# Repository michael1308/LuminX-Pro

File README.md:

# LuminX-WLED
ESP32-based controller for individually addressable LED strips, compatible with WLED firmware.

# Features
-   ESP32-WROOM-32E
-   CH340E/G
-   USB C
-   Micro USB for power
-   2.1mm Barrel Jack w/ reversible polarity    
-   Screw Terminal power input
-   Current Measurement w/ INA219/INA180
-   5V Buck Converter
-   3.3V LDO
-   Microphone
-   IR Receiver
-   2x Digital out w/ Clock signal
-   Power Switching Relay
-   Temperature Sensor DS18B20
-   I2C Connector
-   ESP32 Debug Connector
-   Up to 10A

# Rev 1.0 (03.2023)
## Issues:
- Reverse Polarity Protection MOSFET reversed
- INA180 Resistor too large -> change to 10mOhm
- USBLC6 wrong footprint -> SOT-6

## Changes:
- Remove Micro USB
- Route Input Voltage directly to output
- Change reverse polarity protection to antiparallel diode (M7)
- Integrate PDM Microphone
- Better Integration for IR Sensor
- Better Integration for Temp Sensor
- 4 Output Channels
- Smaller Footprint
- Automotive or Glass fuse?
- Separate board for guitar -> LuminX ??

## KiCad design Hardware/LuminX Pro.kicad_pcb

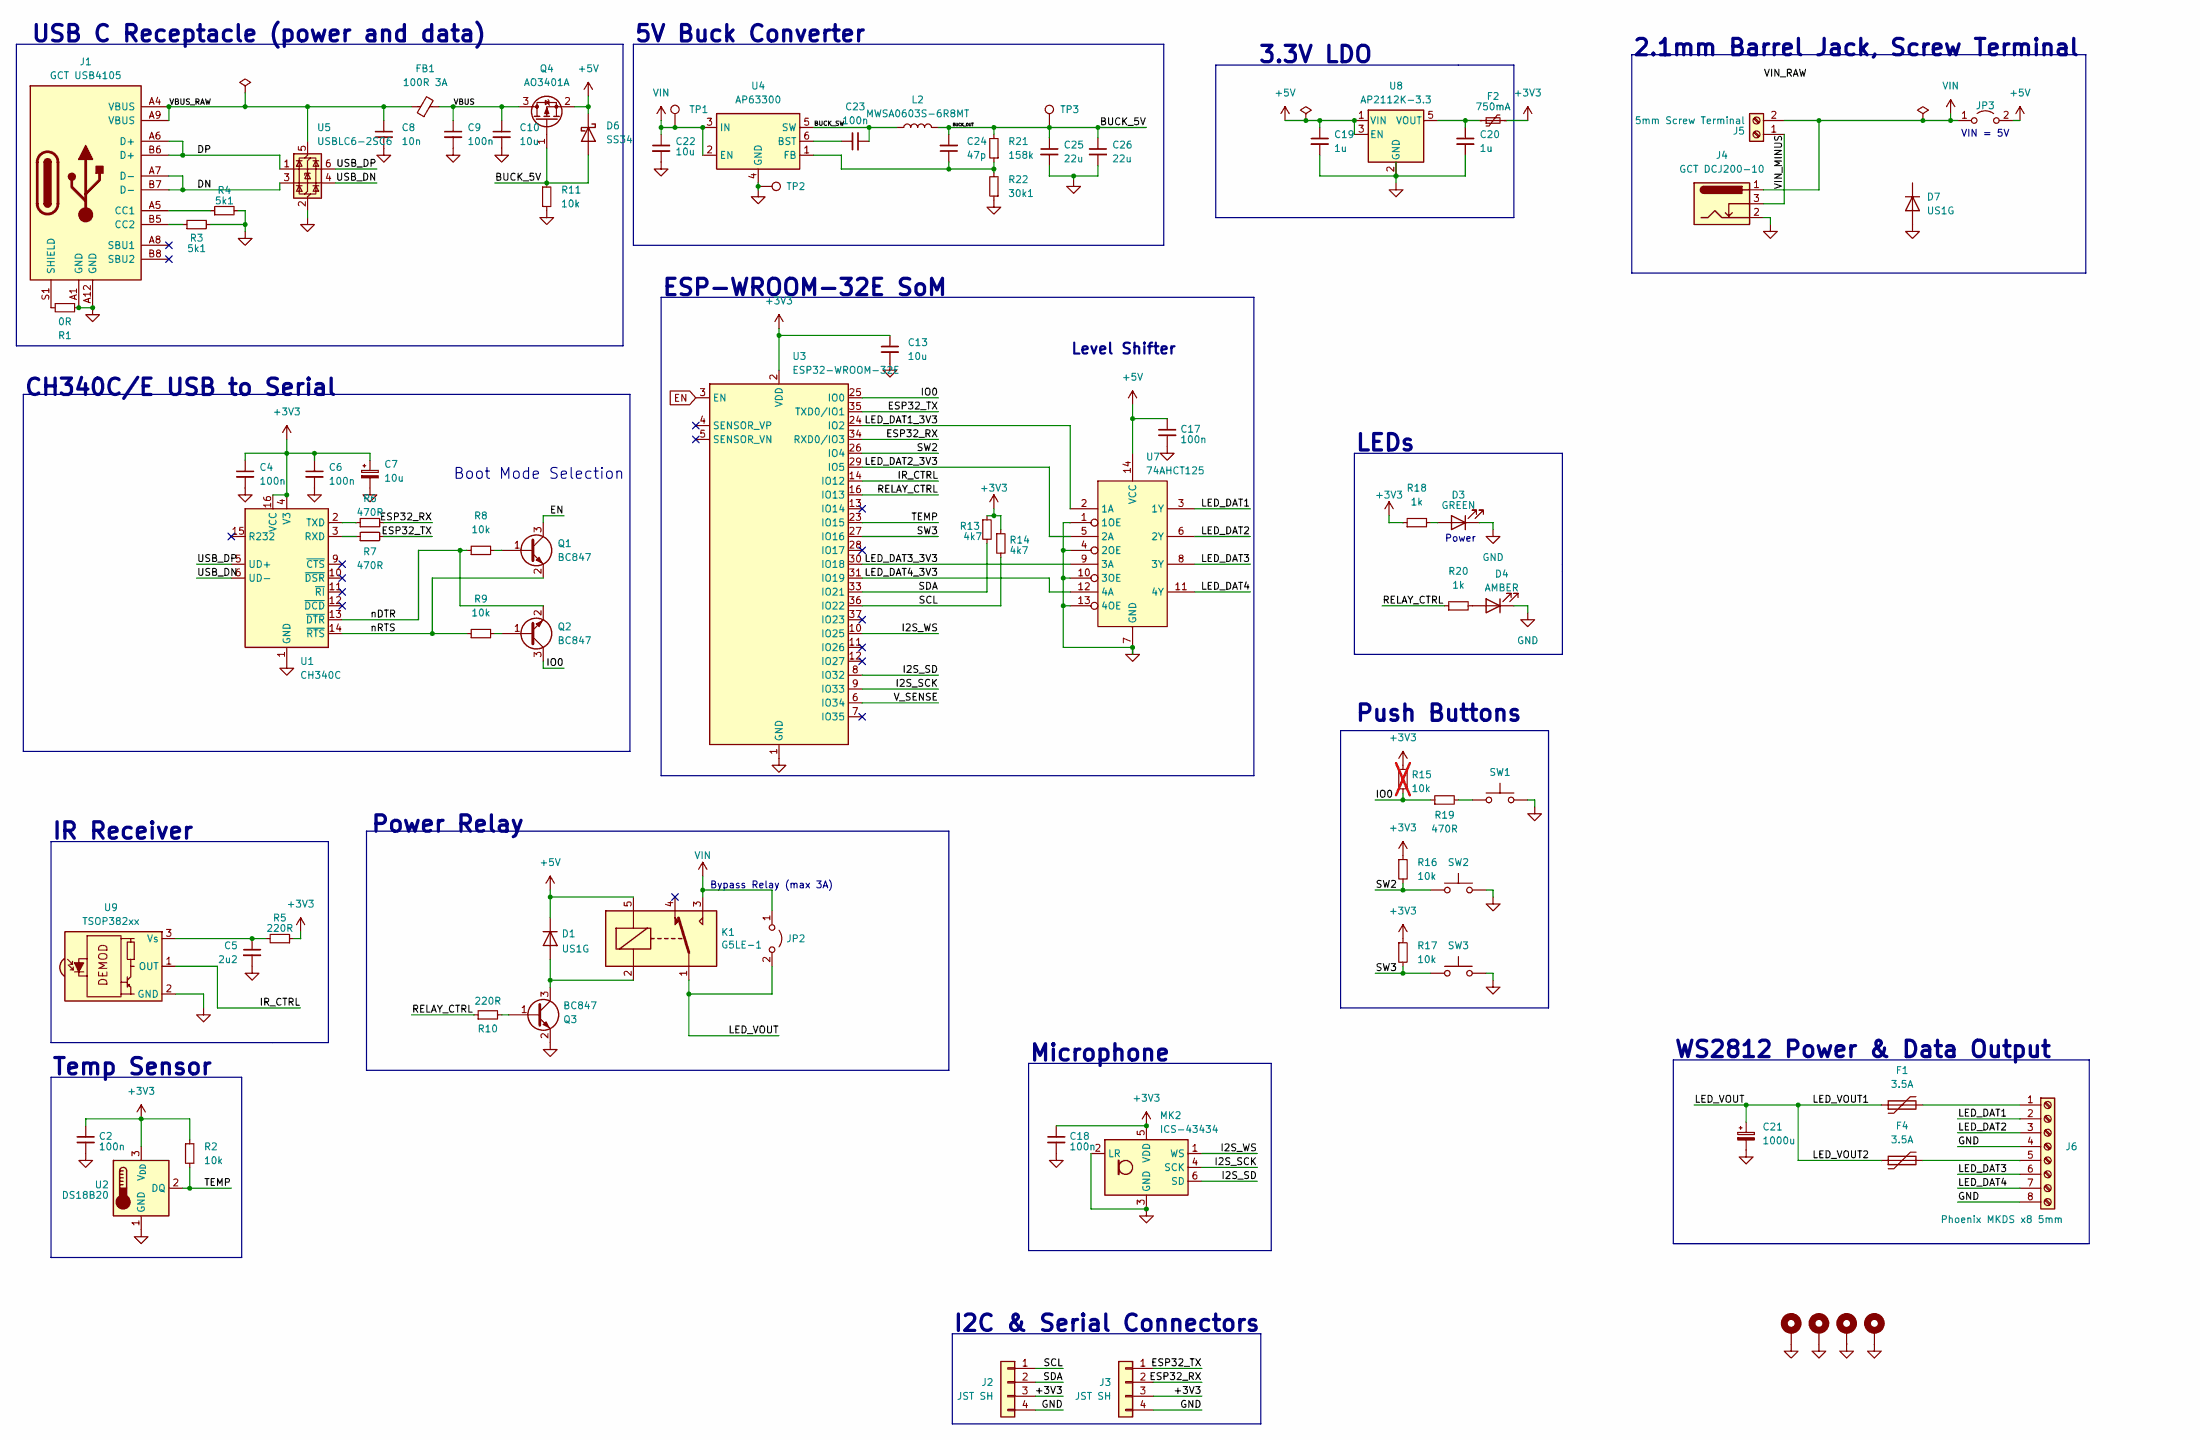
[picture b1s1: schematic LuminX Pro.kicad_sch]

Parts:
C2, C4, C6, C9, C17, C18, C23: 100n; C_0603_1608Metric
C5: 2u2; C_0805_2012Metric
C7, C13: 10u; C_0805_2012Metric
C8: 10n; C_0603_1608Metric
C10, C22: 10u; C_1206_3216Metric
C19, C20: 1u; C_0603_1608Metric
C21: 1000u; CP_Radial_D12.5mm_P5.00mm
C24: 47p; C_0603_1608Metric
C25, C26: 22u; C_1206_3216Metric
D1, D7: US1G; D_SMA
D3: GREEN; LED_0805_2012Metric
D4: AMBER; LED_0805_2012Metric
D6: SS34; D_SMA
F1, F4: 3.5A; Fuseholder_Clip-5x20mm_Littelfuse_521_Lateral_P17.00x5.00mm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
F2: 750mA; Fuse_1206_3216Metric
FB1: 100R 3A; L_0603_1608Metric
H1, H2, H3, H4: MountingHole; MountingHole_3.2mm_M3_Pad_Via
J1: GCT USB4105; USB_C_Receptacle_GCT_USB4105-xx-A_16P_TopMnt_Horizontal
J2, J3: JST SH; JST_SH_BM04B-SRSS-TB_1x04-1MP_P1.00mm_Vertical
J4: GCT DCJ200-10; Conn_BarrelJack_GCT_DCJ200-10-A_Horizontal
J5: 5mm Screw Terminal; TerminalBlock_Phoenix_MKDS-1,5-2_1x02_P5.00mm_Horizontal
J6: Phoenix MKDS x8 5mm; TerminalBlock_Phoenix_MKDS-1,5-8_1x08_P5.00mm_Horizontal
JP2, JP3: Jumper_2_Open; PinHeader_1x02_P2.54mm_Vertical
K1: G5LE-1; Relay_SPDT_Omron-G5LE-1
L2: MWSA0603S-6R8MT; L_Sunlord_MWSA0603S; Part No. SLH1207S330MTT
MK2: ICS-43434; InvenSense_ICS-43434-6_3.5x2.65mm
Q1, Q2, Q3: BC847; SOT-23
Q4: AO3401A; SOT-23
R1: 0R; R_0603_1608Metric
R2, R8, R9, R16, R17: 10k; R_0603_1608Metric
R3, R4: 5k1; R_0603_1608Metric
R5, R10: 220R; R_0603_1608Metric
R6, R7, R19: 470R; R_0603_1608Metric
R11: 10k; R_0805_2012Metric
R13, R14: 4k7; R_0603_1608Metric
R15: 10k; R_0603_1608Metric; not fitted
R18, R20: 1k; R_0603_1608Metric
R21: 158k; R_0603_1608Metric
R22: 30k1; R_0603_1608Metric
SW1, SW2, SW3: SW_Push; SW_SPST_PTS645
TP1, TP2, TP3: TestPoint
U1: CH340C; SOIC-16_3.9x9.9mm_P1.27mm
U2: DS18B20; TO-92_Inline
U3: ESP32-WROOM-32E; ESP32-WROOM-32D
U4: AP63300; TSOT-23-6
U5: USBLC6-2SC6; SOT-23-6
U7: 74AHCT125; SO-14_3.9x8.65mm_P1.27mm
U8: AP2112K-3.3; SOT-23-5
U9: TSOP382xx; Vishay_MINICAST-3Pin

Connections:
+3V3: C2.1, C4.1, C6.1, C7.1, C13.1, C18.1, F2.2, J2.3, J3.3, MK2.5 (VDD), R2.1, R5.1, R13.1, R14.1, R15.1, R16.1, R17.1, R18.1, U1.4 (V3), U1.16 (VCC), U2.3 (V_{DD}), U3.2 (VDD)
+5V: C17.1, C19.1, D1.1 (K), D6.1 (K), JP3.2 (B), K1.5, Q4.2 (S), U7.14 (VCC), U8.1 (VIN), U8.3 (EN)
/BUCK_5V: C24.2, C25.1, C26.1, D6.2 (A), L2.2, Q4.1 (G), R11.1, R21.2, TP3.1
/BUCK_SW: C23.2, L2.1, U4.5 (SW)
/DN: J1.A7 (D-), J1.B7 (D-), U5.3 (I/O2)
/DP: J1.A6 (D+), J1.B6 (D+), U5.1 (I/O1)
/ESP32_RX: J3.2, R6.2, U3.34 (RXD0/IO3)
/ESP32_TX: J3.1, R7.2, U3.35 (TXD0/IO1)
/I2S_SCK: MK2.4 (SCK), U3.9 (IO33)
/I2S_SD: MK2.6 (SD), U3.8 (IO32)
/I2S_WS: MK2.1 (WS), U3.10 (IO25)
/IO0: Q2.3 (C), R15.2, R19.1, U3.25 (IO0)
/IR_CTRL: U3.14 (IO12), U9.1 (OUT)
/LED_DAT1: J6.2, U7.3 (1Y)
/LED_DAT1_3V3: U3.24 (IO2), U7.2 (1A)
/LED_DAT2: J6.3, U7.6 (2Y)
/LED_DAT2_3V3: U3.29 (IO5), U7.5 (2A)
/LED_DAT3: J6.6, U7.8 (3Y)
/LED_DAT3_3V3: U3.30 (IO18), U7.9 (3A)
/LED_DAT4: J6.7, U7.11 (4Y)
/LED_DAT4_3V3: U3.31 (IO19), U7.12 (4A)
/LED_VOUT: C21.1, F1.1, F4.1, JP2.2 (B), K1.1
/RELAY_CTRL: R10.1, R20.1, U3.16 (IO13)
/SCL: J2.1, R14.2, U3.36 (IO22)
/SDA: J2.2, R13.2, U3.33 (IO21)
/SW2: R16.2, SW2.1, U3.26 (IO4)
/SW3: R17.2, SW3.1, U3.27 (IO16)
/TEMP: R2.2, U2.2 (DQ), U3.23 (IO15)
/USB_DN: U1.6 (UD-), U5.4 (I/O2)
/USB_DP: U1.5 (UD+), U5.6 (I/O1)
/VBUS: C9.1, C10.1, FB1.2, Q4.3 (D)
/VBUS_RAW: C8.1, FB1.1, J1.A4 (VBUS), J1.A9 (VBUS), J1.B4 (VBUS), J1.B9 (VBUS), U5.5 (VBUS)
/VIN_MINUS: J4.3, J5.1
/V_SENSE: U3.6 (IO34)
/nDTR: Q2.2 (E), R8.1, U1.13 (~DTR)
/nRTS: Q1.2 (E), R9.1, U1.14 (~RTS)
EN: Q1.3 (C), U3.3 (EN)
GND: C2.2, C4.2, C5.2, C6.2, C7.2, C8.2, C9.2, C10.2, C13.2, C17.2, C18.2, C19.2, C20.2, C21.2, C22.2, C25.2, C26.2, D3.1 (K), D4.1 (K), D7.2 (A), H1.1, H2.1, H3.1, H4.1, J1.A1 (GND), J1.A12 (GND), J1.B1 (GND), J1.B12 (GND), J2.4, J3.4, J4.2, J6.4, J6.8, MK2.2 (LR), MK2.3 (GND), Q3.2 (E), R1.1, R3.2, R4.2, R11.2, R22.1, SW1.2, SW2.2, SW3.2, TP2.1, U1.1 (GND), U2.1 (GND), U3.1 (GND), U3.15 (GND), U3.38 (GND), U3.39 (GND), U4.4 (GND), U5.2 (GND), U7.1 (1OE), U7.4 (2OE), U7.7 (GND), U7.10 (3OE), U7.13 (4OE), U8.2 (GND), U9.2 (GND)
unnamed: D1.2 (A), K1.2, Q3.3 (C)
unnamed: D3.2 (A), R18.2
unnamed: D4.2 (A), R20.2
unnamed: J1.A5 (CC1), R4.1
unnamed: J1.B5 (CC2), R3.1
unnamed: J1.S1 (SHIELD), R1.2
unnamed: F1.2, J6.1
unnamed: F4.2, J6.5
unnamed: Q1.1 (B), R8.2
unnamed: Q2.1 (B), R9.2
unnamed: Q3.1 (B), R10.2
unnamed: R19.2, SW1.1
unnamed: R7.1, U1.3 (RXD)
unnamed: R6.1, U1.2 (TXD)
unnamed: C23.1, U4.6 (BST)
unnamed: C24.1, R21.1, R22.2, U4.1 (FB)
unnamed: C20.1, F2.1, U8.5 (VOUT)
unnamed: C5.1, R5.2, U9.3 (Vs)
VIN: C22.1, J4.1, J5.2, JP2.1 (A), JP3.1 (A), K1.3, TP1.1, U4.2 (EN), U4.3 (IN)

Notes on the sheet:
5V Buck Converter
I2C & Serial Connectors
Level Shifter
USB C Receptacle (power and data)
WS2812 Power & Data Output
Bypass Relay (max 3A)
Power
Power Relay
3.3V LDO
IR Receiver
LEDs
Boot Mode Selection
Microphone
VIN = 5V
ESP-WROOM-32E SoM
2.1mm Barrel Jack, Screw Terminal
Push Buttons
Temp Sensor
CH340C/E USB to Serial

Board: 4 copper layers, 79 parts (3 on the bottom side), 56 nets, no tracks yet.

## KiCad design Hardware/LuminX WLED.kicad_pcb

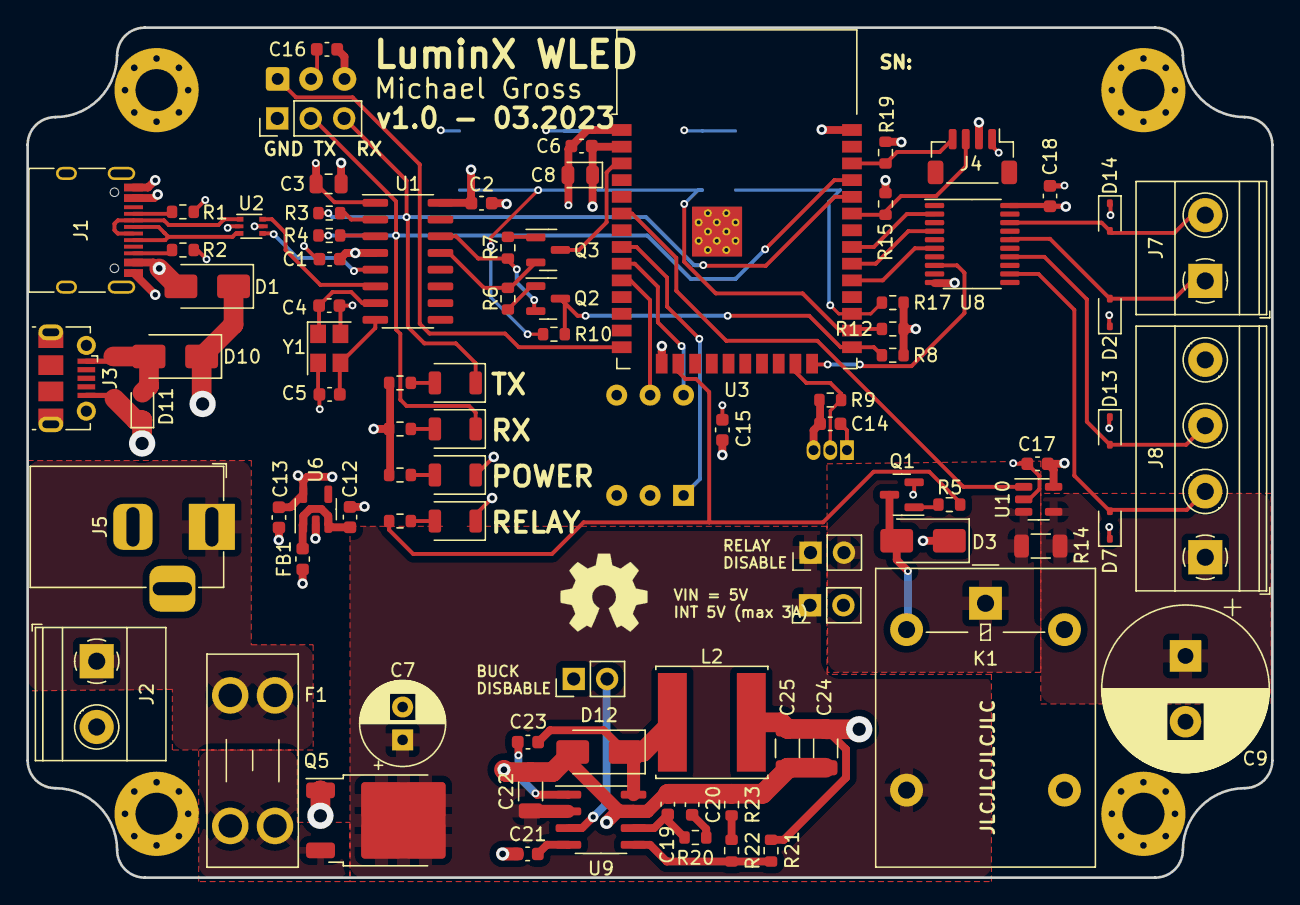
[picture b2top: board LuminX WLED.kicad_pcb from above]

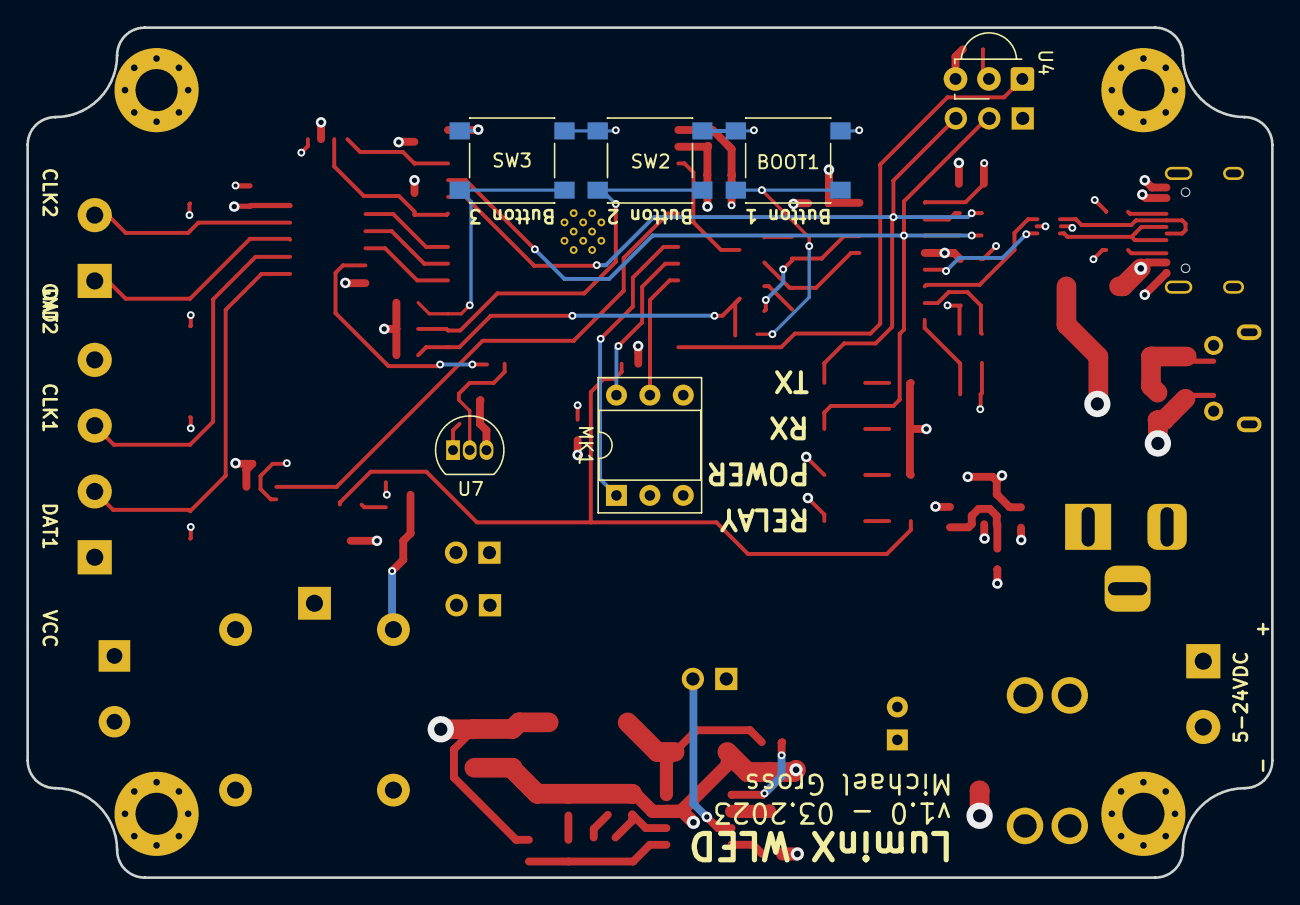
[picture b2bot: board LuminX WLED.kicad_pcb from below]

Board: 4 copper layers, 94.6 x 64.6 mm, 96 parts (6 on the bottom side), 63 nets.

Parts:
BOOT1: SW_Push; SW_SPST_PTS645
C1, C2, C6, C14, C15, C16, C17, C18, C23: 100n; C_0603_1608Metric
C3: 10u; C_0805_2012Metric
C4, C5: 30p; C_0603_1608Metric
C7: 100u/35V; CP_Radial_D6.3mm_P2.50mm
C8: 10u; D_0805_2012Metric
C9: 1000u; CP_Radial_D12.5mm_P5.00mm
C12, C13: 1u; C_0603_1608Metric
C19: 10p; C_0603_1608Metric
C20: 1n; C_0603_1608Metric
C21: 8n2; C_0603_1608Metric
C22: 10u; C_1206_3216Metric
C24, C25: 22u; C_1206_3216Metric
D1, D10: SS34; D_SMA
D2, D7, D11, D13, D14: SD05; D_SOD-323
D3: US1G; D_SMA
D4: YELLOW; LED_1206_3216Metric_ReverseMount_Hole1.8x2.4mm
D5, D6: GREEN; LED_1206_3216Metric_ReverseMount_Hole1.8x2.4mm
D9: AMBER; LED_1206_3216Metric_ReverseMount_Hole1.8x2.4mm
D12: SS54; D_SMA
F1: 10A; Fuseholder_Blade_Mini_Keystone_3568
FB1: 100R; L_0603_1608Metric
H1, H2, H3, H4: MountingHole; MountingHole_3.2mm_M3_Pad_Via
J1: USB_C_Receptacle_USB2.0; USB_C_Receptacle_HRO_TYPE-C-31-M-12
J2, J7: 5mm Screw Terminal; TerminalBlock_Phoenix_MKDS-1,5-2_1x02_P5.00mm_Horizontal
J3: USB_B_Micro; USB_Micro-B_Molex-105017-0001
J4: Conn_01x04_Pin; JST_SH_BM04B-SRSS-TB_1x04-1MP_P1.00mm_Vertical
J5: Barrel_Jack_Switch; BarrelJack_Horizontal
J8: 5mm Screw Terminal; TerminalBlock_Phoenix_MKDS-1,5-4_1x04_P5.00mm_Horizontal
J9: Conn_01x03_Pin; PinHeader_1x03_P2.54mm_Vertical
JP1, JP2, JP3: Jumper_2_Open; PinHeader_1x02_P2.54mm_Vertical
K1: G5LE-1; Relay_SPDT_Omron-G5LE-1
L2: 10u/3A; L_Sunlord_SWPA8040S
MK1: INMP441; DIP-6_W7.62mm_Socket
Q1, Q2, Q3: BC847; SOT-23
Q5: IRF5305; TO-252-2
R1, R2: 5k1; R_0603_1608Metric
R3, R4, R10: 470R; R_0603_1608Metric
R5: 220R; R_0603_1608Metric
R6, R7, R8, R9, R12, R17, R21: 10k; R_0603_1608Metric
R11, R13, R16, R18: 1k; R_0603_1608Metric
R14: 0.1R; R_1206_3216Metric
R15, R19: 4k7; R_0603_1608Metric
R20: 33k; R_0603_1608Metric
R22: 1k2; R_0603_1608Metric
R23: 680; R_0603_1608Metric
SW2, SW3: SW_Push; SW_SPST_PTS645
U1: CH340G; SOIC-16_3.9x9.9mm_P1.27mm
U2: USBLC6-2P6; SOT-666
U3: ESP32-WROOM-32D
U4: TSOP382xx; Vishay_MINICAST-3Pin
U6: AP2112K-3.3; SOT-23-5
U7: DS18B20; TO-92_Inline
U8: 74AHCT244; TSSOP-20_4.4x6.5mm_P0.65mm
U9: TPS54332; SOIC-8_3.9x4.9mm_P1.27mm
U10: INA180A1; SOT-23-5
Y1: 12MHz; Crystal_SMD_3225-4Pin_3.2x2.5mm

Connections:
+3V3: C1.1, C2.1, C3.1, C6.1, C8.1, C13.1, C14.1, C15.1, C16.1, C17.1, J4.2, MK1.2 (VDD), R8.1, R9.1, R11.1, R12.1, R13.1, R15.1, R16.1, R17.1, R19.1, U1.4 (V3), U1.16 (VCC), U3.2 (VDD), U4.3 (Vs), U6.5 (VOUT), U7.3 (V_{DD}), U10.5 (V+)
+5V: C18.1, C24.1, C25.1, D1.1 (K), D3.1 (K), D10.1 (K), FB1.1, JP3.2 (B), K1.5, L2.2, R21.2, U8.20 (VCC)
/ESP32+CH340/CH340_XI: C4.1, U1.7 (XI), Y1.1
/ESP32+CH340/CH340_XO: C5.1, U1.8 (XO), Y1.3
/ESP32+CH340/nDTR: Q3.2 (E), R6.1, U1.13 (~DTR)
/ESP32+CH340/nRTS: Q2.2 (E), R7.1, U1.14 (~RTS)
/Power+USB/D+: J1.A6 (D+), J1.B6 (D+), U2.3 (I/O2)
/Power+USB/D-: J1.A7 (D-), J1.B7 (D-), U2.1 (I/O1)
/Power+USB/INA180_IN: JP2.2 (B), K1.1, R14.1, U10.3 (+)
/Power+USB/VBUS_MICROUSB: D10.2 (A), D11.2 (A2), J3.1 (VBUS)
/Power+USB/VBUS_USBC: D1.2 (A), J1.A4 (VBUS), J1.A9 (VBUS), J1.B4 (VBUS), J1.B9 (VBUS), U2.5 (VBUS)
/Power+USB/VIN_RAW: F1.1, J2.1, J5.1
/Power+USB/VIN_RPP: F1.2, Q5.3 (S)
CLK1: D13.2 (A2), J8.3, U8.14 (1Y2)
CLK1_3V3: U3.29 (IO5), U8.6 (1A2)
CLK2: D14.2 (A2), J7.2, U8.18 (1Y0)
CLK2_3V3: U3.31 (IO19), U8.2 (1A0)
DAT1: D7.2 (A2), J8.2, U8.12 (1Y3)
DAT1_3V3: U3.24 (IO2), U8.8 (1A3)
DAT2: D2.2 (A2), J7.1, U8.16 (1Y1)
DAT2_3V3: U3.30 (IO18), U8.4 (1A1)
EN: Q3.3 (C), U3.3 (EN)
ESP32_RX: D5.1 (K), J9.3, R3.2, U3.34 (RXD0/IO3)
ESP32_TX: D4.1 (K), J9.2, R4.2, U3.35 (TXD0/IO1)
GND: BOOT1.2, C1.2, C2.2, C3.2, C4.2, C5.2, C6.2, C7.2, C8.2, C9.2, C12.2, C13.2, C14.2, C15.2, C16.2, C17.2, C18.2, C19.2, C20.2, C21.2, C22.2, C24.2, C25.2, D2.1 (A1), D6.1 (K), D7.1 (A1), D9.1 (K), D11.1 (A1), D12.2 (A), D13.1 (A1), D14.1 (A1), H1.1, H2.1, H3.1, H4.1, J1.A1 (GND), J1.A12 (GND), J1.B1 (GND), J1.B12 (GND), J2.2, J3.5 (GND), J4.1, J5.2, J8.4, J9.1, JP1.1 (A), MK1.3 (GND), MK1.4 (L/R), Q1.2 (E), Q5.1 (G), R1.2, R2.2, R23.1, SW2.2, SW3.2, U1.1 (GND), U2.2 (GND), U3.1 (GND), U3.15 (GND), U3.38 (GND), U3.39 (GND), U4.2 (GND), U6.2 (GND), U7.1 (GND), U8.10 (GND), U9.7 (GND), U10.2 (GND), Y1.2, Y1.4
IO0: Q2.3 (C), R8.2, R10.1, U3.25 (IO0)
IR_CTRL: U3.14 (IO12), U4.1 (OUT)
unnamed: C12.1, FB1.2, U6.1 (VIN), U6.3 (EN)
unnamed: BOOT1.1, R10.2
unnamed: C20.1, R20.1
unnamed: D3.2 (A), K1.2, Q1.3 (C)
unnamed: D4.2 (A), R11.2
unnamed: D5.2 (A), R13.2
unnamed: D6.2 (A), R16.2
unnamed: D9.2 (A), R18.2
unnamed: C23.2, D12.1 (K), L2.1, U9.8 (PH)
unnamed: J1.A5 (CC1), R1.1
unnamed: J1.B5 (CC2), R2.1
unnamed: JP1.2 (B), U9.3 (EN)
unnamed: Q1.1 (B), R5.2
unnamed: Q2.1 (B), R6.2
unnamed: Q3.1 (B), R7.2
unnamed: R22.1, R23.2
unnamed: R4.1, U1.3 (RXD)
unnamed: R3.1, U1.2 (TXD)
unnamed: C23.1, U9.1 (BOOT)
unnamed: C19.1, R20.2, U9.6 (COMP)
unnamed: C21.1, U9.4 (SS)
unnamed: R21.1, R22.2, U9.5 (VSENSE)
RELAY_CTRL: R5.1, R18.1, U3.16 (IO13)
SCK: MK1.6 (SCK), U3.9 (IO33)
SCL: J4.4, R19.2, U3.36 (IO22)
SD: MK1.1 (SD), U3.8 (IO32)
SDA: J4.3, R15.2, U3.33 (IO21)
SW2: R12.2, SW2.1, U3.26 (IO4)
SW3: R17.2, SW3.1, U3.27 (IO16)
TEMP: R9.2, U3.23 (IO15), U7.2 (DQ)
USB_D+: U1.5 (UD+), U2.4 (I/O2)
USB_D-: U1.6 (UD-), U2.6 (I/O1)
VIN: C7.1, C22.1, JP2.1 (A), JP3.1 (A), K1.3, Q5.2 (D), U9.2 (VIN)
VOUT_LED: C9.1, J8.1, R14.2, U10.4 (-)
V_SENSE: U3.6 (IO34), U10.1
WS: MK1.5 (WS), U3.10 (IO25)

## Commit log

2023-04-01 Rev 1.0
2023-04-15 v1.0
2024-05-31 Restructure project
2024-05-31 Revise v2 schematic
2024-12-15 Add backups
